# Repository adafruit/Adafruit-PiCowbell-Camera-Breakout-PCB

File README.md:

## Adafruit PiCowbell Camera Breakout PCB

<a href="http://www.adafruit.com/products/5945"><br/>
Click here to purchase one from the Adafruit shop</a>

PCB files for the Adafruit PiCowbell Camera Breakout. 

Format is EagleCAD schematic and board layout
* https://www.adafruit.com/product/5945
* https://www.adafruit.com/product/5946
* https://www.adafruit.com/product/5947
* https://www.adafruit.com/product/5949
* https://www.adafruit.com/product/5948

### Description

Ding dong! Hear that? It's the PiCowbell ringing, letting you know that the new Adafruit PiCowbell OV5640 Camera Breakout with 72-Degree Lens and Autofocus is in stock.

This is a quality OV5640 camera with a 5 Megapixel sensor element, a 72-degree non-distorting lens, and autofocus motor, plus all the support circuitry you need to start taking pictures with your Pico or Pico W. You can grab raw RGB images for image analysis, or use the built in JPEG encoding to save images to an SD card or upload them to adafruit.io.

The RP2040 chip has a fast PIO interface peripheral and enough memory to interface with 'DVP' (8-bit parallel digital) cameras. These camera sensors have 8 image data pins, Pixel Clock, H Sync and V Sync signals, plus I2C configuration interface and a Reset plus power Down pin. That does mean a lot of GPIO are used! But we still have 6 GPIO pin available even after adding an SD cart and shutter button.

Camera PiCowbell Features:

* Interface for OV5640 Camera module
VSync: GPIO 0
Power Down: GPIO 1
HSync: GPIO 2
Pixel Clock: GPIO 3
SDA/SCL: GPIO 4 and GPIO 5
8-bit Digital: GPIO6 through GPIO 13
Reset: GPIO 14
VMotor connected to 3.3V for auto-focus modules
* Micro SD Card:
SPI on GPIO 16, GPIO 18 and GPIO 19
Chip select on GPIO 17
Optional SD Detect on GPIO 15
* Shutter button on GPIO 22
* Reset button
* 16 MHz 'XClock' generated by onboard oscillator
* Stemma QT port for I2C on GPIO 4 / 5

There are multiple variants of this board. Each has a different camera module:

* [Autofocus 72 Degree Lens](https://www.adafruit.com/product/5945)
* [Autofocus 120 Degree Lens](https://www.adafruit.com/product/5946)
* [Wide Angle 160 Degree Lens](https://www.adafruit.com/product/5947) - No auto-focus, fixed 'infinite' focus module
* [Wide Angle 120 Degree Lens](https://www.adafruit.com/product/5949) - No auto-focus, fixed 'infinite' focus module
* [120 Degree Low Distortion](https://www.adafruit.com/product/5948) - No auto-focus, fixed 'infinite' focus module

Note that to use the auto-focusing capability with the auto-focus modules, you need to load a new firmware binary over I2C. The autofocus system is controlled with I2C commands to begin an auto-focus procedure and determine that focus is complete. Otherwise, the camera looks just like any other OV5640 sensor.

Each order comes with an assembled PCB, camera sensor, and two pieces of 20-pin pin header. You will need to solder in the header yourself, but it's a quick task.

Since this board has the camera pointing 'up', it's best to use our PiCowbell 'doubler' to have the Pico on one side with the BOOT button accessible, and then the camera on the other side. Or you can 'stack' the camera 'bell on top, best when you don't need easy access to the BOOT loading button.

Or, for a compact package, you can...

Use the Pico Stacking Headers if you want to be able to plug into a breadboard or other accessory with sockets. Solder these onto the Pico so that the camera is on top.
Use the Pico Socket Headers if you want to plug directly in and have a nice solid connection that doesn't have any poking-out-bits. Ditto, solder these into the Pico and plug the camera on top.

### License

Adafruit invests time and resources providing this open source design, please support Adafruit and open-source hardware by purchasing products from [Adafruit](https://www.adafruit.com)!

Designed by Limor Fried/Ladyada for Adafruit Industries.

Creative Commons Attribution/Share-Alike, all text above must be included in any redistribution. 
See license.txt for additional details.

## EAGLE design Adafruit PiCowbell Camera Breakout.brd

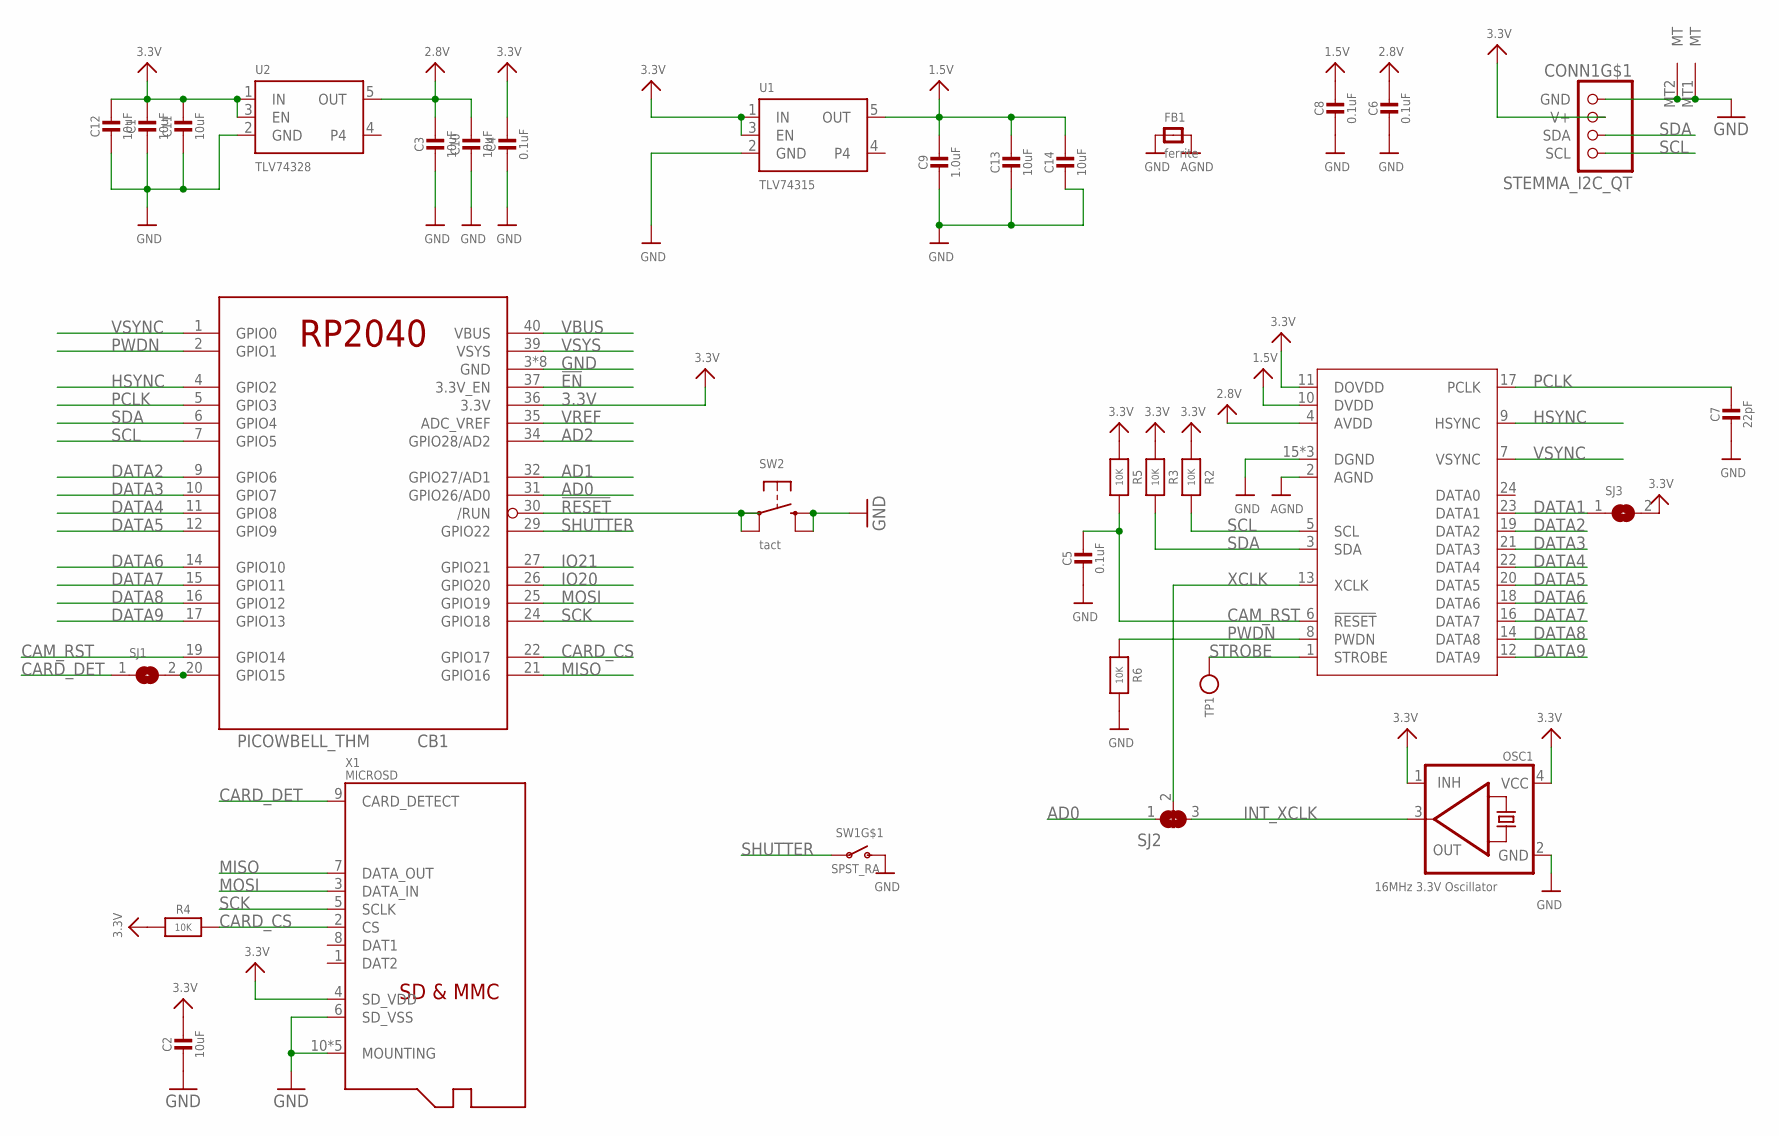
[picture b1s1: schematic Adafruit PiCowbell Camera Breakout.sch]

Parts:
C1, C2, C3, C10, C11, C12, C13, C14: 10uF; 0805-NO
C4, C5, C6, C8: 0.1uF; _0402NO
C7: 22pF; _0402NO
C9: 1.0uF; 0603-NO
CB1: PICOWBELL_THM
CONN1: STEMMA_I2C_QT; JST_SH4
FB1: ferrite; 0603-NO
OSC1: 16MHz 3.3V Oscillator; OSC_3.2X2.5MM
R2, R3, R4, R5, R6: 10K; _0402NO
SJ1: SOLDERJUMPER; SOLDERJUMPER_ARROW_NOPASTE
SJ2: SOLDERJUMPER_2WAY; SOLDERJUMPER_2WAY_OPEN_NOPASTE
SJ3: SOLDERJUMPERCLOSED; SOLDERJUMPER_CLOSEDWIRE
SW1: SPST_RA; SPST_TACTILE_RA_2*4*3.5MM
SW2: tact; BTN_RKB2_4.6X2.8
TP1: TESTPOINTROUND1.5MM; TESTPOINT_ROUND_1.5MM
U1: TLV74315; SOT23-5; JLC_ROTATION 0
U2: TLV74328; SOT23-5; JLC_ROTATION 0
X1: MICROSD; MOLEX_104031-0811
X2: CAMERA_OV2640_SLIM; OV2640FSL_SLIM

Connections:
1.5V: C8.1, C9.1, C13.1, C14.1, U1.5 (OUT), X2.10 (DVDD)
2.8V: C3.1, C6.1, C10.1, U2.5 (OUT), X2.4 (AVDD)
3.3V: C1.1, C2.1, C4.1, C11.1, C12.1, CB1.36 (3.3V), CONN1.2 (V+), OSC1.1 (INH), OSC1.4 (VCC), R2.1, R3.1, R4.1, R5.1, SJ3.2, U1.1 (IN), U1.3 (EN), U2.1 (IN), U2.3 (EN), X1.4 (SD_VDD), X2.11 (DOVDD)
!EN: CB1.37 (3.3V_EN)
!RESET: CB1.30 (/RUN), SW2.A, SW2.A' (P1)
AD0: CB1.31 (GPIO26/AD0), SJ2.1
AD1: CB1.32 (GPIO27/AD1)
AD2: CB1.34 (GPIO28/AD2)
AGND: FB1.2, X2.2 (AGND)
CAM_RST: C5.1, CB1.19 (GPIO14), R5.2, X2.6 (!RESET)
CARD_CS: CB1.22 (GPIO17), R4.2, X1.2 (CS)
CARD_DET: SJ1.1, X1.9 (CARD_DETECT)
DATA1: SJ3.1, X2.23 (DATA1)
DATA2: CB1.9 (GPIO6), X2.19 (DATA2)
DATA3: CB1.10 (GPIO7), X2.21 (DATA3)
DATA4: CB1.11 (GPIO8), X2.22 (DATA4)
DATA5: CB1.12 (GPIO9), X2.20 (DATA5)
DATA6: CB1.14 (GPIO10), X2.18 (DATA6)
DATA7: CB1.15 (GPIO11), X2.16 (DATA7)
DATA8: CB1.16 (GPIO12), X2.14 (DATA8)
DATA9: CB1.17 (GPIO13), X2.12 (DATA9)
GND: C1.2, C2.2, C3.2, C4.2, C5.2, C6.2, C7.2, C8.2, C9.2, C10.2, C11.2, C12.2, C13.2, C14.2, CB1.3 (GND), CB1.8 (GND), CB1.13 (GND), CB1.18 (GND), CB1.23 (GND), CB1.28 (GND), CB1.33 (GND), CB1.38 (GND), CONN1.1 (GND), CONN1.MT1 (MT), CONN1.MT2 (MT), FB1.1, OSC1.2 (GND), R6.2, SW1.2 (S), SW2.B (S), SW2.B' (S1), U1.2 (GND), U2.2 (GND), X1.6 (SD_VSS), X1.10 (MOUNTING), X1.G1 (MOUNTING), X1.G2 (MOUNTING), X1.G3 (MOUNTING), X1.G4 (MOUNTING), X2.15 (DGND), X2.SPRT1 (DGND), X2.SPRT2 (DGND)
HSYNC: CB1.4 (GPIO2), X2.9 (HSYNC)
INT_XCLK: OSC1.3 (OUT), SJ2.3
IO20: CB1.26 (GPIO20)
IO21: CB1.27 (GPIO21)
MISO: CB1.21 (GPIO16), X1.7 (DATA_OUT)
MOSI: CB1.25 (GPIO19), X1.3 (DATA_IN)
unnamed: CB1.20 (GPIO15), SJ1.2
PCLK: C7.1, CB1.5 (GPIO3), X2.17 (PCLK)
PWDN: CB1.2 (GPIO1), R6.1, X2.8 (PWDN)
SCK: CB1.24 (GPIO18), X1.5 (SCLK)
SCL: CB1.7 (GPIO5), CONN1.4 (SCL), R2.2, X2.5 (SCL)
SDA: CB1.6 (GPIO4), CONN1.3 (SDA), R3.2, X2.3 (SDA)
SHUTTER: CB1.29 (GPIO22), SW1.1
STROBE: TP1.P$1, X2.1 (STROBE)
VBUS: CB1.40 (VBUS)
VREF: CB1.35 (ADC_VREF)
VSYNC: CB1.1 (GPIO0), X2.7 (VSYNC)
VSYS: CB1.39 (VSYS)
XCLK: SJ2.2, X2.13 (XCLK)

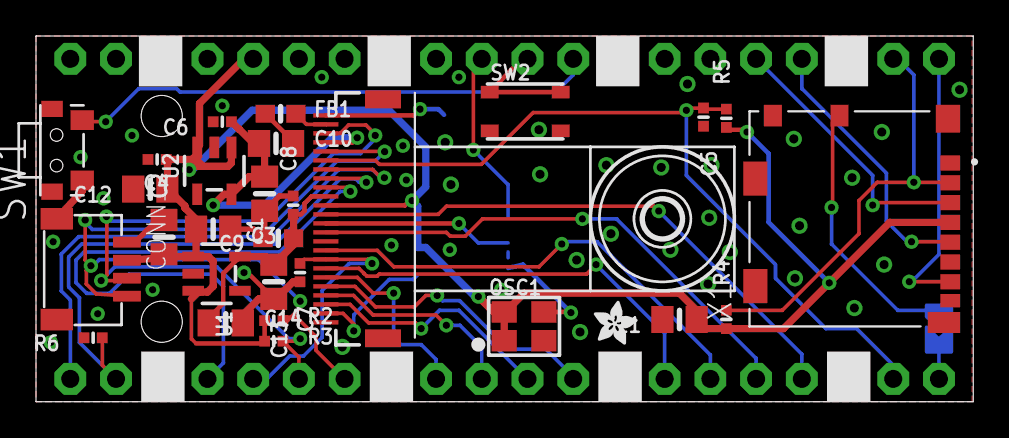
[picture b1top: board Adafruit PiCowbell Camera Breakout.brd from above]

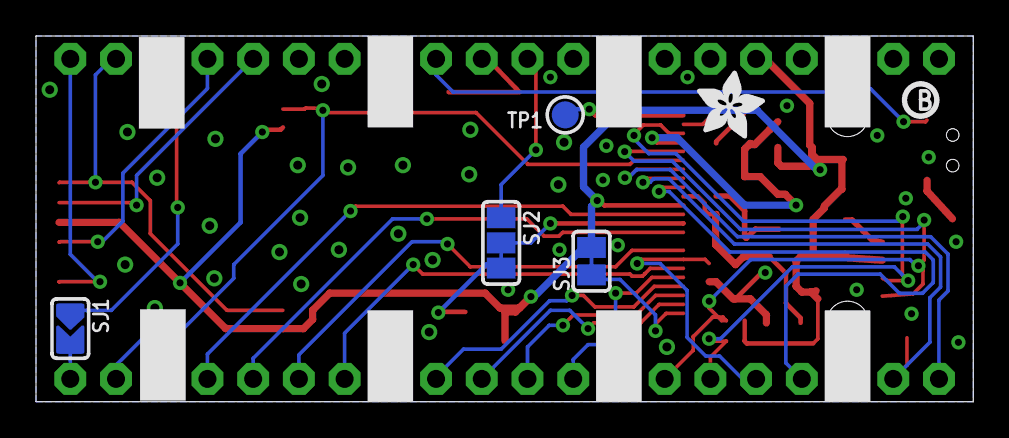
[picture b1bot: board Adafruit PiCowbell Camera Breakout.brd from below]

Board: 2 copper layers, 52.1 x 20.3 mm, 93 parts (33 on the bottom side), 33 nets.

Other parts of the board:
PLABEL54: PLABEL54
PLABEL55: PLABEL55
PLABEL56: PLABEL56
PLABEL57: PLABEL57
PLABEL58: PLABEL58
PLABEL59: PLABEL59
PLABEL60: PLABEL60
PLABEL61: PLABEL61
PLABEL62: PLABEL62
PLABEL63: PLABEL63
PLABEL64: PLABEL64
PLABEL65: PLABEL65
PLABEL66: PLABEL66
PLABEL67: PLABEL67
PLABEL68: PLABEL68
PLABEL69: PLABEL69
PLABEL70: PLABEL70
PLABEL71: PLABEL71
PLABEL72: PLABEL72
PLABEL73: PLABEL73
PLABEL74: PLABEL74
PLABEL75: PLABEL75
PLABEL76: PLABEL76
PLABEL77: PLABEL77
PLABEL78: PLABEL78
PLABEL79: PLABEL79
PLABEL80: PLABEL80
PLABEL81: PLABEL81
PLABEL82: PLABEL82
PLABEL83: PLABEL83
PLABEL84: PLABEL84
PLABEL85: PLABEL85
PLABEL86: PLABEL86
PLABEL88: PLABEL88
PLABEL89: PLABEL89
PLABEL90: PLABEL90
PLABEL91: PLABEL91
PLABEL92: PLABEL92
PLABEL93: PLABEL93
PLABEL94: PLABEL94
PLABEL95: PLABEL95
PLABEL96: PLABEL96
PLABEL97: PLABEL97
PLABEL98: PLABEL98
PLABEL99: PLABEL99
PLABEL100: PLABEL100
PLABEL101: PLABEL101
PLABEL102: PLABEL102
PLABEL103: PLABEL103
PLABEL104: PLABEL104
PLABEL107: PLABEL107
PLABEL108: PLABEL108
PLABEL109: PLABEL109
PLABEL110: PLABEL110
PLABEL111: PLABEL111
PLABEL112: PLABEL112
PLABEL113: PLABEL113
U$10: ADAFRUIT_3.5MM
U$11: ADAFRUIT_2.5MM
U$12: PCBFEAT-REV-040

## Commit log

2024-05-03 cookiecutter

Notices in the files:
parts and their libraries:
microbuilder: This work is placed in the public domain, and may be freely used for commercial and non-commercial work with the following conditions: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
